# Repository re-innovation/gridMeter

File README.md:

# gridMeter
A National Grid frequency monitor for visualising power flows on the national grid

# Overview

# Collaborators
* James Fowkes - Software and PCB design v1
* Matt Little - PCB design v2 and Hardware

# PCB
This holds the PCB files done using KiCAD
http://kicad-pcb.org/

# Software
This holds the software. Uploaded via the Arduino IDE.
This is programmed to an ATTiny84
It requires

# Hardware
This holds the mechanical files for the enclosure.

# To DO

- Update PCB design with changes
- Enclosure design - version 1 done

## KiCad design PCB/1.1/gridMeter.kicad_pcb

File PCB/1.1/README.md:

# mains-freq-meter
A mains frequency gauge with moving coil readout

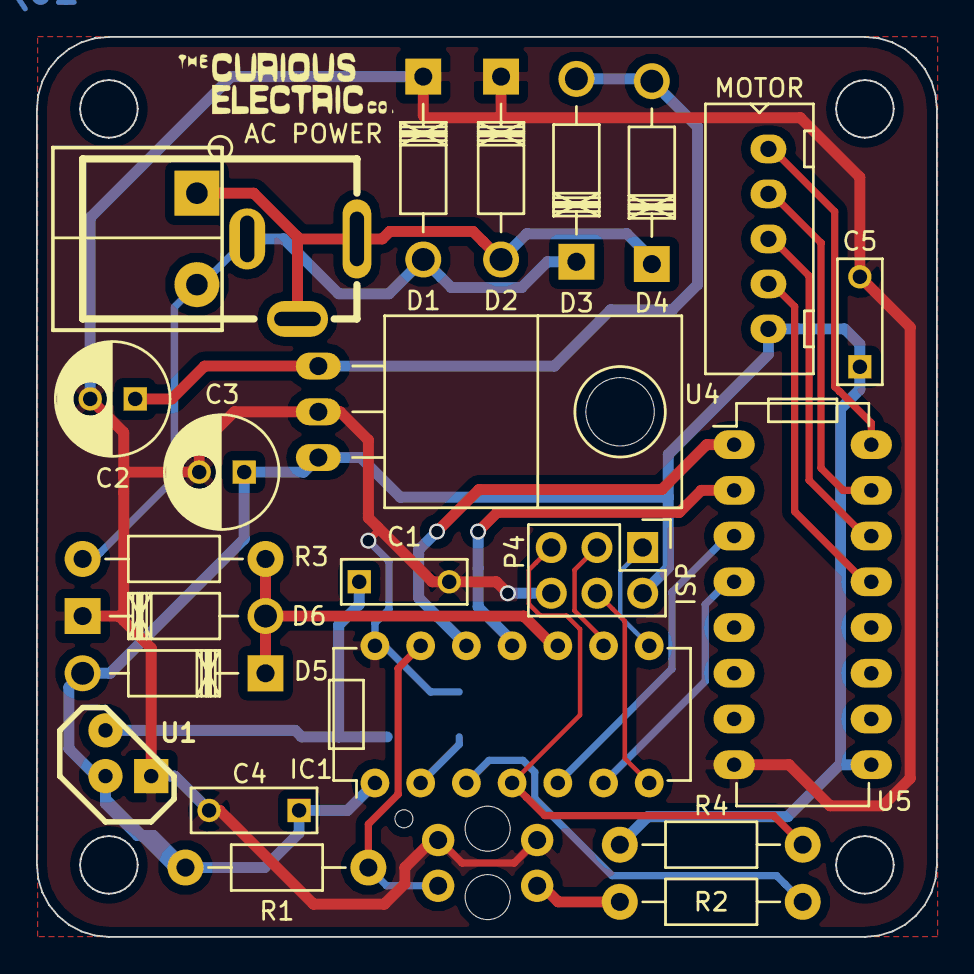
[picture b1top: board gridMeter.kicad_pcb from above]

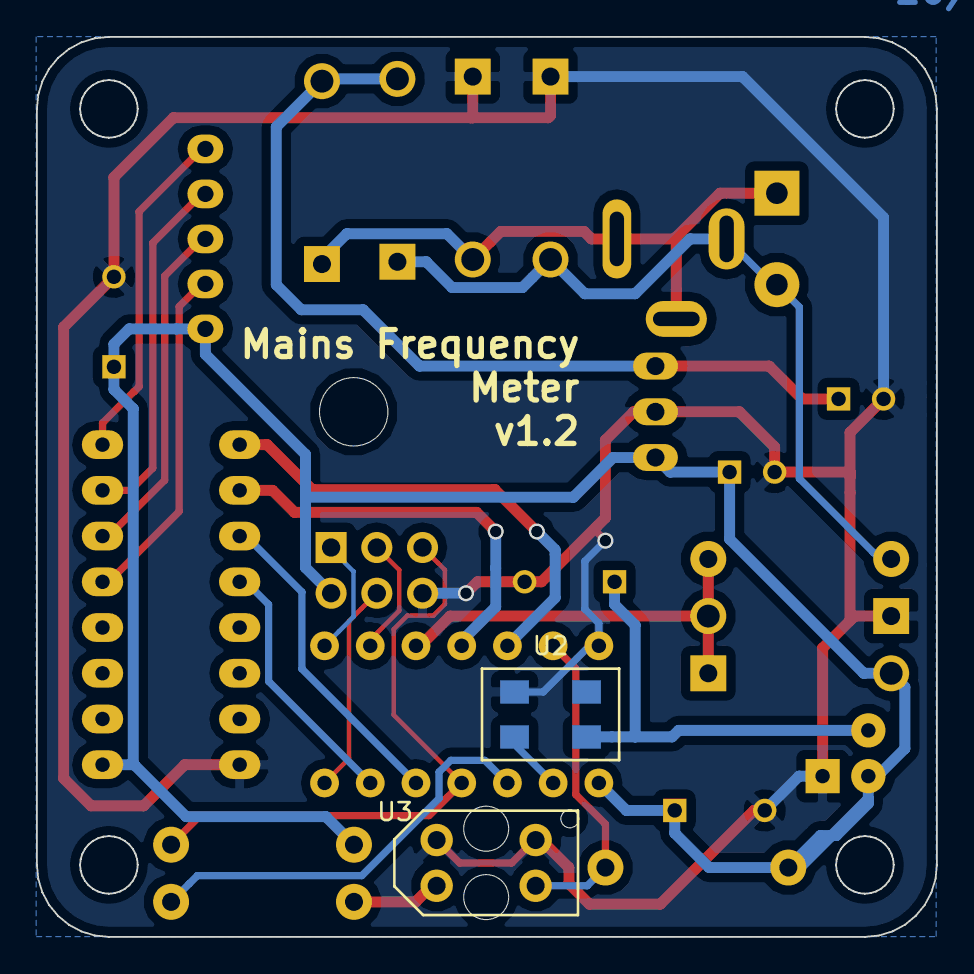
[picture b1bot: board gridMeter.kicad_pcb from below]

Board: 2 copper layers, 50.0 x 50.0 mm, 26 parts (2 on the bottom side), 23 nets.

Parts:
C1, C4, C5: 100n; C_Rect_L7_W2.5_P5
C2, C3: 220u; C_Radial_D6.3_L11.2_P2.5
CON1: AC POWER; DC_Power_2_1
D1, D2, D3, D4, D5: IN400x; Diode_DO-41_SOD81_Horizontal_RM10
D6: 1N400x; Diode_DO-41_SOD81_Horizontal_RM10
IC1: ATTINY84A-PU; DIP-14_W7.62mm
P2: AC POWER; TH_CONN_2W
P3: MOTOR; XHP-5
P4: ISP; Pin_Header_Straight_2x03
P6: LOGO1; CuriousElectric_flat_12mm
R1, R3, R4: 10K; Resistor_Horizontal_RM10mm
R2: 330R; Resistor_Horizontal_RM10mm
U1: MCP170-3_3V; TO92-MCP1700
U2: TCXO_SMD_4P; FOX924
U3: TCRT5000
U4: 7805; TO-220_Neutral123_Horizontal
U5: ULN2003; DIP-16_W7.62mm_LongPads

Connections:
/DMAINSF: D5.1, D6.2, IC1.10, R3.1
/IN1: IC1.12, U5.1
/IN2: IC1.11, U5.2
/IN3: IC1.5, U5.3
/IN4: IC1.6, U5.4
/MAINSF: CON1.1, D1.2, D3.1, P2.2, R3.2
/MISO: IC1.8, P4.1
/MOSI: IC1.7, P4.4
/MOTOR_HOME_OUT: IC1.3, R2.1
/MOTOR_HOME_SENSE: IC1.13, R1.1, U3.1
/RST: IC1.4, P4.5, R4.1
/SCK: IC1.9, P4.3
/TCXO: IC1.2, U2.3
GND: C1.2, C2.2, C3.2, C4.2, C5.2, D1.1, D2.1, D6.1, IC1.14, P4.6, U1.GND, U2.2, U3.2, U3.3, U4.2, U5.8
unnamed: C1.1, U1.VO, U2.4
unnamed: C2.1, D3.2, D4.2, U4.1
unnamed: CON1.2, CON1.3, D2.2, D4.1, P2.1
unnamed: P3.1, U5.16
unnamed: P3.2, U5.15
unnamed: P3.3, U5.14
unnamed: P3.4, U5.13
unnamed: R2.2, U3.4
VCC: C3.1, C4.1, C5.1, D5.2, IC1.1, P3.5, P4.2, R1.2, R4.2, U1.VI, U4.3, U5.9

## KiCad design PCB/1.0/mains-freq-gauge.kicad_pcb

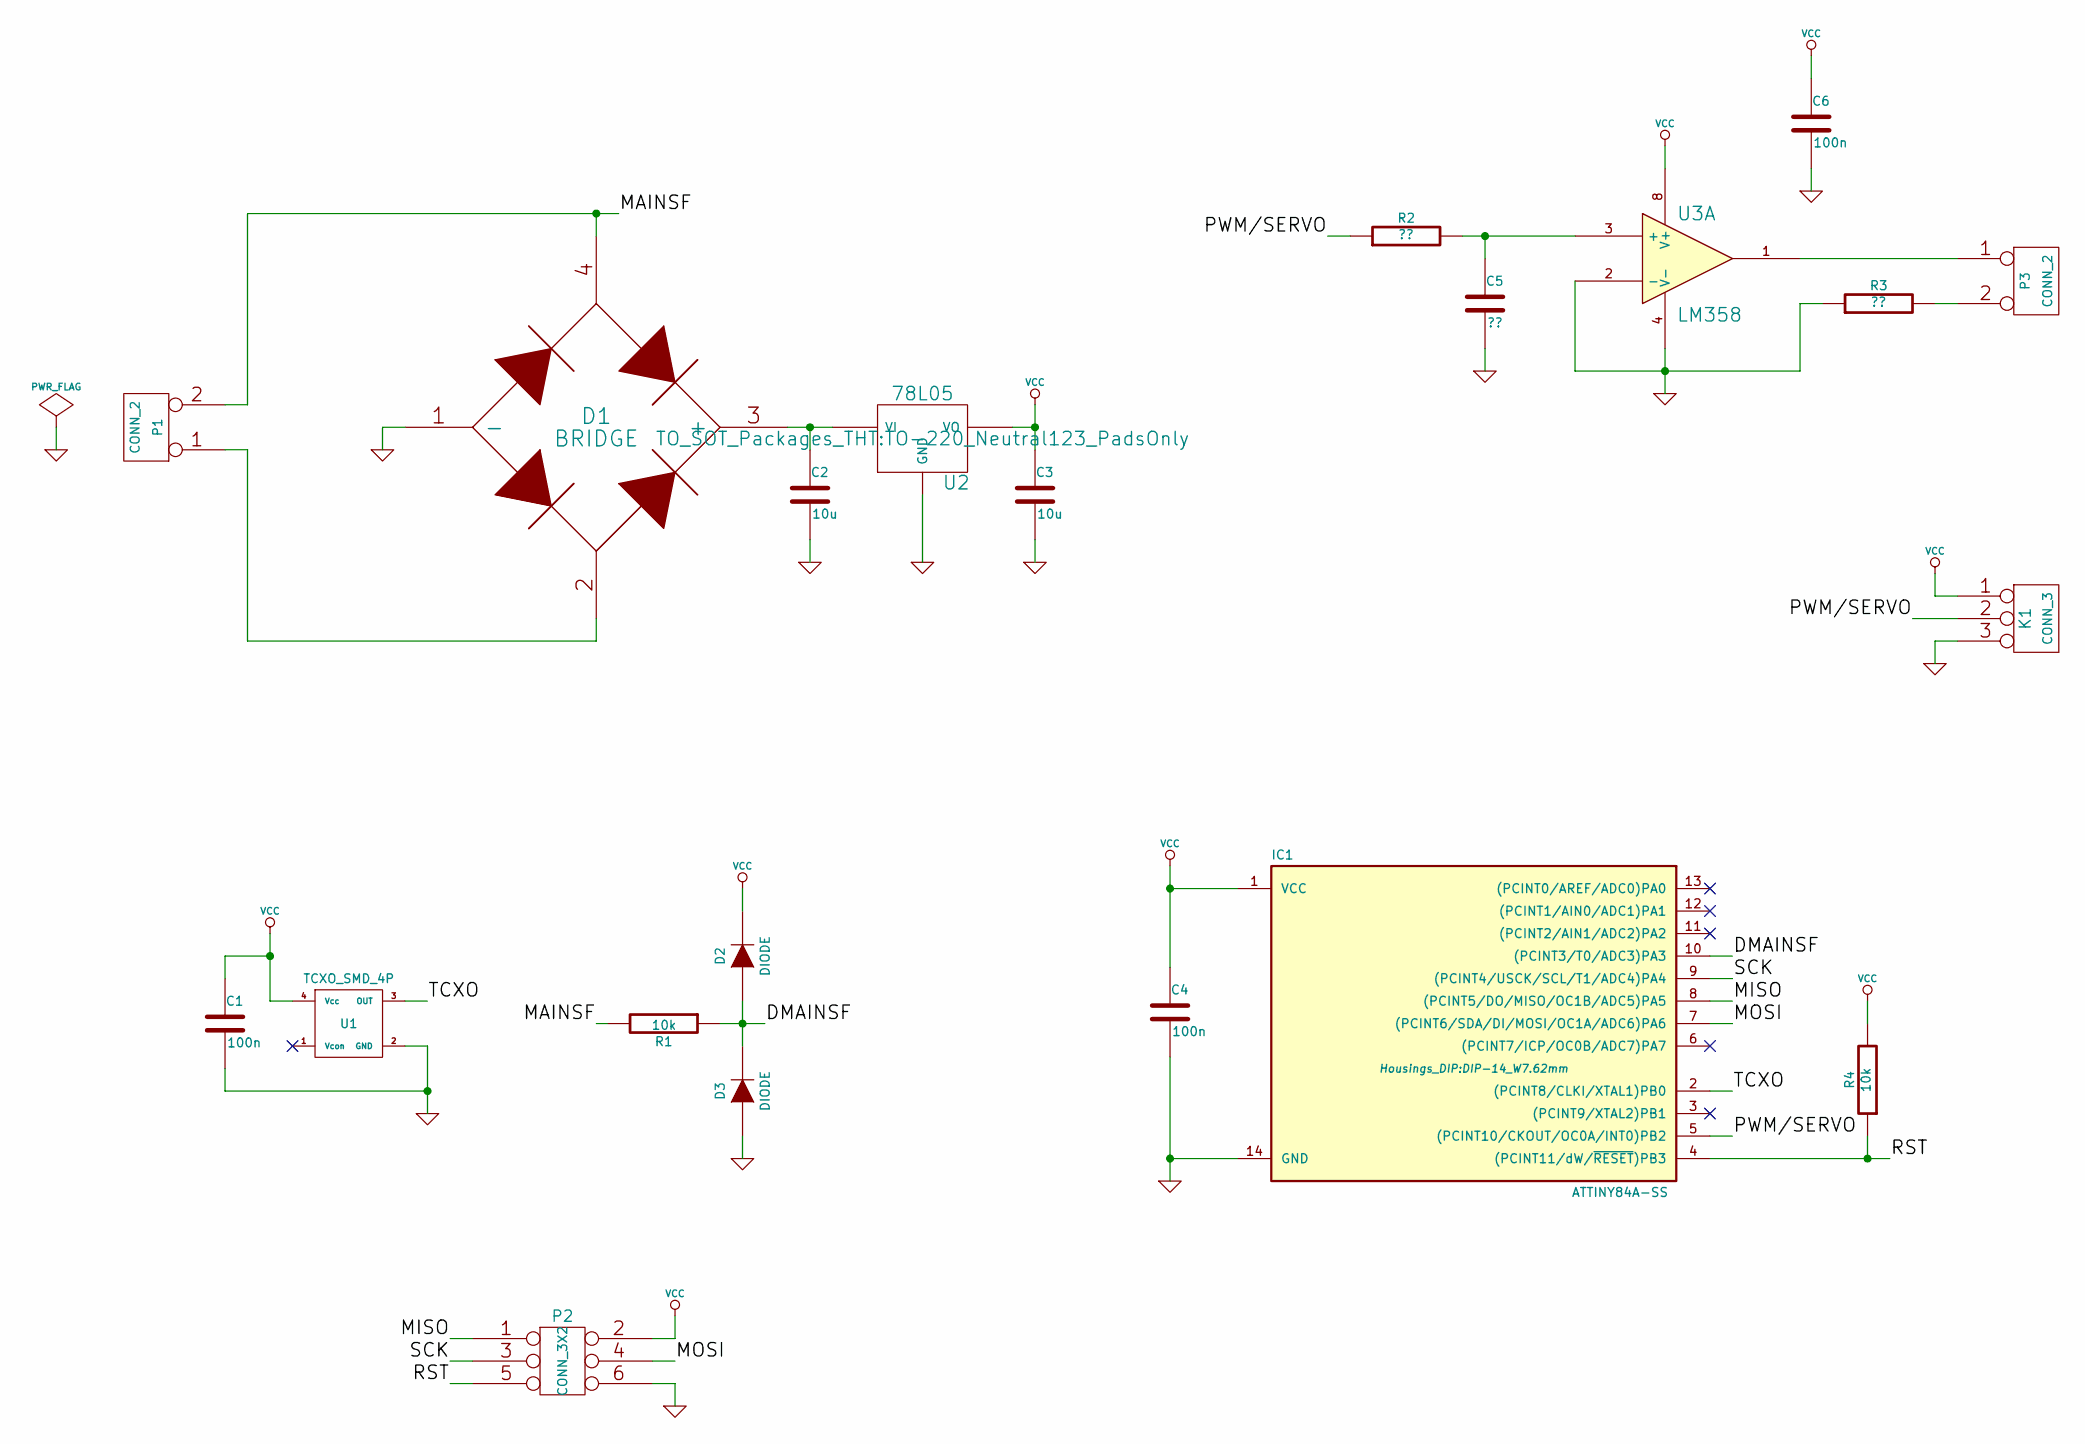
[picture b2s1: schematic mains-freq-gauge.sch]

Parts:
C1, C4, C6: 100n; C_Rect_L4_W2.5_P2.5
C2, C3: 10u; C_Radial_D5_L11_P2.5
C5: ??; C_Rect_L4_W2.5_P2.5
D1: BRIDGE; WOB
D2, D3: DIODE; Diode_DO-41_SOD81_Horizontal_RM10
IC1: ATTINY84A-SS; DIP-14_W7.62mm
K1: CONN_3; Pin_Header_Straight_1x03
P1, P3: CONN_2; Pin_Header_Straight_1x02
P2: CONN_3X2; Pin_Header_Straight_2x03
R1, R4: 10k; Resistor_Horizontal_RM15mm
R2, R3: ??; Resistor_Horizontal_RM15mm
U1: TCXO_SMD_4P; TG5006CG
U2: 78L05; TO-220_Neutral123_PadsOnly
U3: LM358; DIP-8_W7.62mm

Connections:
/DMAINSF: D2.1 (A), D3.2 (K), IC1.10 ((PCINT3/T0/ADC3)PA3), R1.1
/MAINSF: D1.4, P1.2 (PM), R1.2
/MISO: IC1.8 ((PCINT5/DO/MISO/OC1B/ADC5)PA5), P2.1
/MOSI: IC1.7 ((PCINT6/SDA/DI/MOSI/OC1A/ADC6)PA6), P2.4
/PWM/SERVO: IC1.5 ((PCINT10/CKOUT/OC0A/INT0)PB2), K1.2 (PM), R2.1
/RST: IC1.4 ((PCINT11/dW/~RESET~)PB3), P2.5, R4.1
/SCK: IC1.9 ((PCINT4/USCK/SCL/T1/ADC4)PA4), P2.3
/TCXO: IC1.2 ((PCINT8/CLKI/XTAL1)PB0), U1.3 (OUT)
GND: C1.2, C2.2, C3.2, C4.2, C5.2, C6.2, D1.1 (-), D3.1 (A), IC1.14 (GND), K1.3, P2.6, R3.1, U1.2 (GND), U2.2 (GND), U3.2 (-), U3.4 (V-)
unnamed: C2.1, D1.3 (+), U2.3 (VI)
unnamed: C5.1, R2.2, U3.3 (+)
unnamed: D1.2, P1.1
unnamed: P3.1, U3.1
unnamed: P3.2 (PM), R3.2
VCC: C1.1, C3.1, C4.1, C6.1, D2.2 (K), IC1.1 (VCC), K1.1, P2.2, R4.2, U1.4 (Vcc), U2.1 (VO), U3.8 (V+)

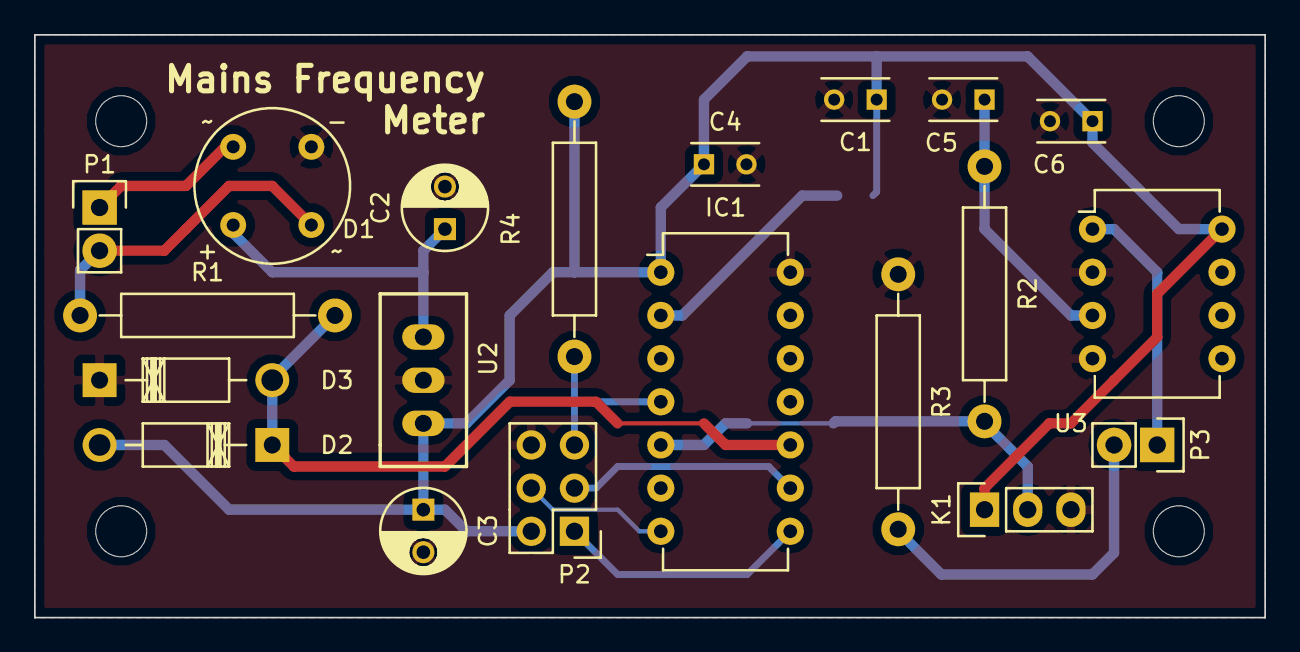
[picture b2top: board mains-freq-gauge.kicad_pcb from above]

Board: 2 copper layers, 72.4 x 34.3 mm, 21 parts (1 on the bottom side), 15 nets.

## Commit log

2016-05-27 Sorting project overview
2016-05-27 Initial PCB and software commit
2016-06-06 PCB version 1.1
2016-06-10 Changes to Schematic PCB Gerbers
    Matt Little changes to components - added different values and suppliers
    codes. Slight change to PCB and footprints. Added Logo to silkscreen.
2016-06-17 Final changes before PCB run 1
2017-03-07 Add homing code, switch to half stepping
2017-03-20 Add lots of comments
2017-03-20 Add movement deadzone and stepper disable
2017-03-23 UPdate with deadband and analog level
2017-03-30 Made software serial object non-static, made format ptr const
2017-03-30 Add homing, movement deadzone stepper enable/disable
